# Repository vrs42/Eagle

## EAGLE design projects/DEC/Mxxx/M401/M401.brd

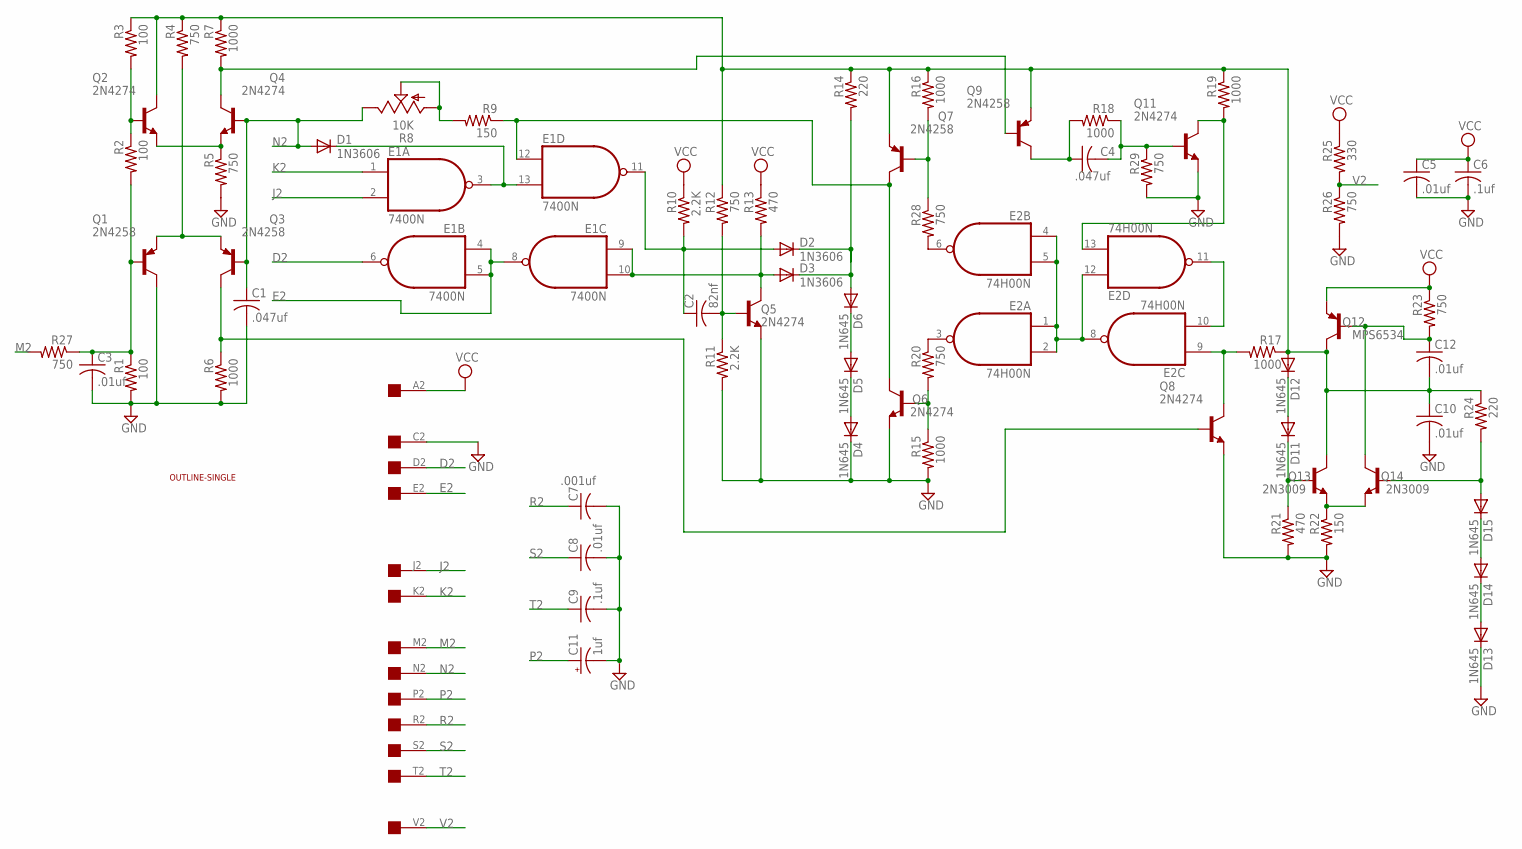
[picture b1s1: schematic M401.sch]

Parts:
C1, C4: .047uf; C050-025X075
C2: 82nf; C050-025X075
C3, C5, C8, C10, C12: .01uf; C050-025X075
C6, C9: .1uf; C050-025X075
C7: .001uf; C050-025X075
C11: 1uf; E15-5
D1, D2, D3: 1N3606; DO35-10
D4, D5, D6, D11, D12, D13, D14, D15: 1N645; DO35-10
E1: 7400N; DIL14
E2: 74H00N; DIL14
Q1, Q3, Q7, Q9: 2N4258; TO39
Q2, Q4, Q5, Q6, Q8, Q11: 2N4274; TO39
Q12: MPS6534; TO39
Q13, Q14: 2N3009; TO39
R1, R2, R3: 100; 0207/10
R4, R5, R12, R20, R23, R26, R27, R28, R29: 750; 0207/10
R6, R7, R15, R16, R17, R18, R19: 1000; 0207/10
R8: 10K; PT-SPIN
R9, R22: 150; 0207/10
R10, R11: 2.2K; 0207/10
R13, R21: 470; 0207/10
R14, R24: 220; 0207/10
R25: 330; 0207/10
U$1: OUTLINE-SINGLE; SINGLE
U$2: EDGE-1; EDGE-CON1

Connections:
D2: E1.6 (O), U$2.D2
E2: E1.4 (I0), E1.5 (I1), E1.8 (O), U$2.E2
GND: C1.2, C3.2, C5.2, C6.2, C7.2, C8.2, C9.2, C10.2, C11.-, D4.C, D13.C, E1.7 (GND), E2.7 (GND), Q1.3 (C), Q5.1 (E), Q6.1 (E), Q8.1 (E), Q11.1 (E), R1.2, R5.2, R6.2, R11.2, R15.2, R21.2, R22.2, R26.2, R29.2, U$2.C2
J2: E1.2 (I1), U$2.J2
K2: E1.1 (I0), U$2.K2
M2: R27.2, U$2.M2
N2: C1.1, D1.A, Q3.2 (B), Q4.2 (B), R8.E, U$2.N2
unnamed: D14.A, D15.C
unnamed: D13.A, D14.C
unnamed: D15.A, Q14.2 (B), R24.2
unnamed: C12.1, Q12.2 (B), Q14.3 (C), R23.2
unnamed: C10.1, C12.2, D12.A, Q2.3 (C), Q7.1 (E), Q9.1 (E), Q12.3 (C), Q13.3 (C), R3.1, R4.1, R7.1, R12.1, R14.1, R16.1, R17.1, R19.1, R24.1
unnamed: D11.C, Q13.2 (B), R21.1
unnamed: Q13.1 (E), Q14.1 (E), R22.1
unnamed: D11.A, D12.C
unnamed: E2.1 (I0), E2.2 (I1), E2.4 (I0), E2.5 (I1), E2.8 (O), E2.12 (I0)
unnamed: C3.1, Q1.2 (B), R1.1, R2.2, R27.1
unnamed: D3.A, E1.9 (I0), E1.10 (I1), Q5.3 (C), R13.2
unnamed: D1.C, E1.3 (O), E1.13 (I1)
unnamed: D4.A, D5.C
unnamed: E2.10 (I1), E2.11 (O)
unnamed: E2.9 (I0), Q8.3 (C), R17.2
unnamed: E2.3 (O), R20.1
unnamed: E2.6 (O), R28.2
unnamed: Q7.2 (B), R16.2, R28.1
unnamed: Q6.2 (B), R15.1, R20.2
unnamed: D5.A, D6.C
unnamed: E1.12 (I0), Q6.3 (C), Q7.3 (C), R9.1
unnamed: C4.1, Q9.3 (C), R18.2
unnamed: C4.2, Q11.2 (B), R18.1, R29.1
unnamed: E2.13 (I1), Q11.3 (C), R19.2
unnamed: D2.C, D3.C, D6.A, R14.2
unnamed: R8.A, R8.S, R9.2
unnamed: C2.2, Q5.2 (B), R11.1, R12.2
unnamed: Q3.3 (C), Q8.2 (B), R6.1
unnamed: C2.1, D2.A, E1.11 (O), R10.2
unnamed: Q1.1 (E), Q3.1 (E), R4.2
unnamed: Q4.3 (C), Q9.2 (B), R7.2
unnamed: Q2.2 (B), R2.1, R3.2
unnamed: Q2.1 (E), Q4.1 (E), R5.1
P2: C11.+, U$2.P2
R2: C7.1, U$2.R2
S2: C8.1, U$2.S2
T2: C9.1, U$2.T2
V2: R25.2, R26.1, U$2.V2
VCC: C5.1, C6.1, E1.14 (VCC), E2.14 (VCC), Q12.1 (E), R10.1, R13.1, R23.1, R25.1, U$2.A2

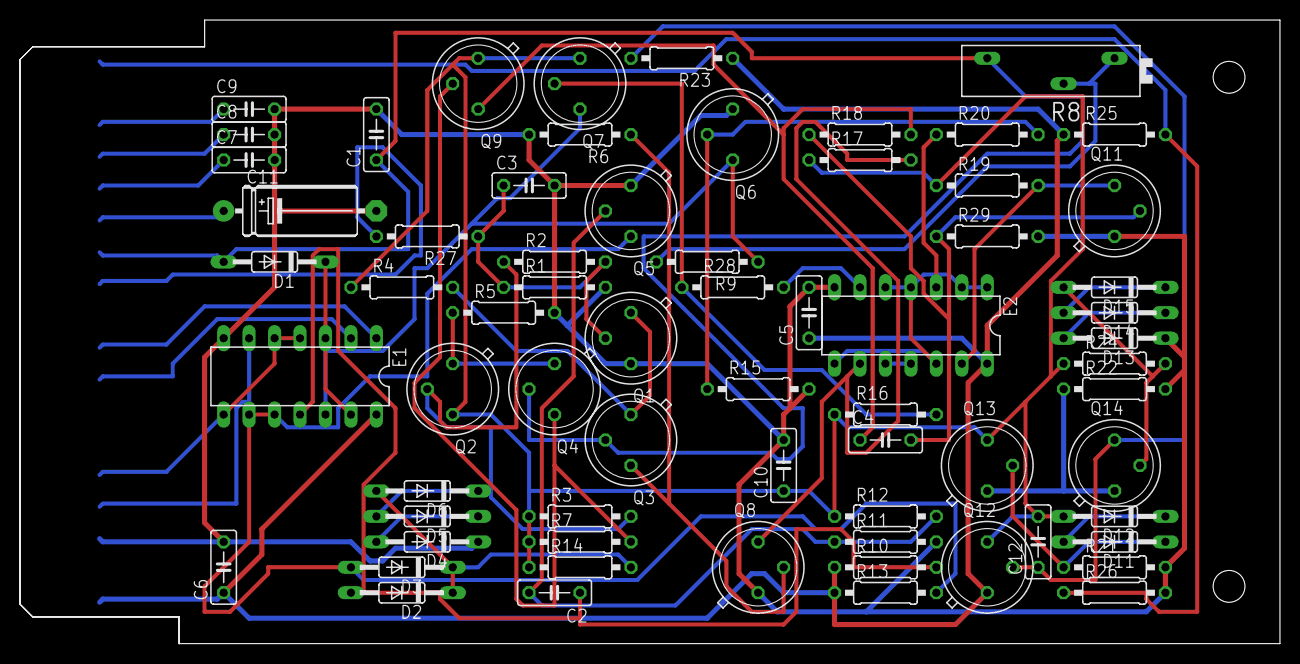
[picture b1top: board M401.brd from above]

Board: 2 copper layers, 125.7 x 62.2 mm, 69 parts (0 on the bottom side), 46 nets.

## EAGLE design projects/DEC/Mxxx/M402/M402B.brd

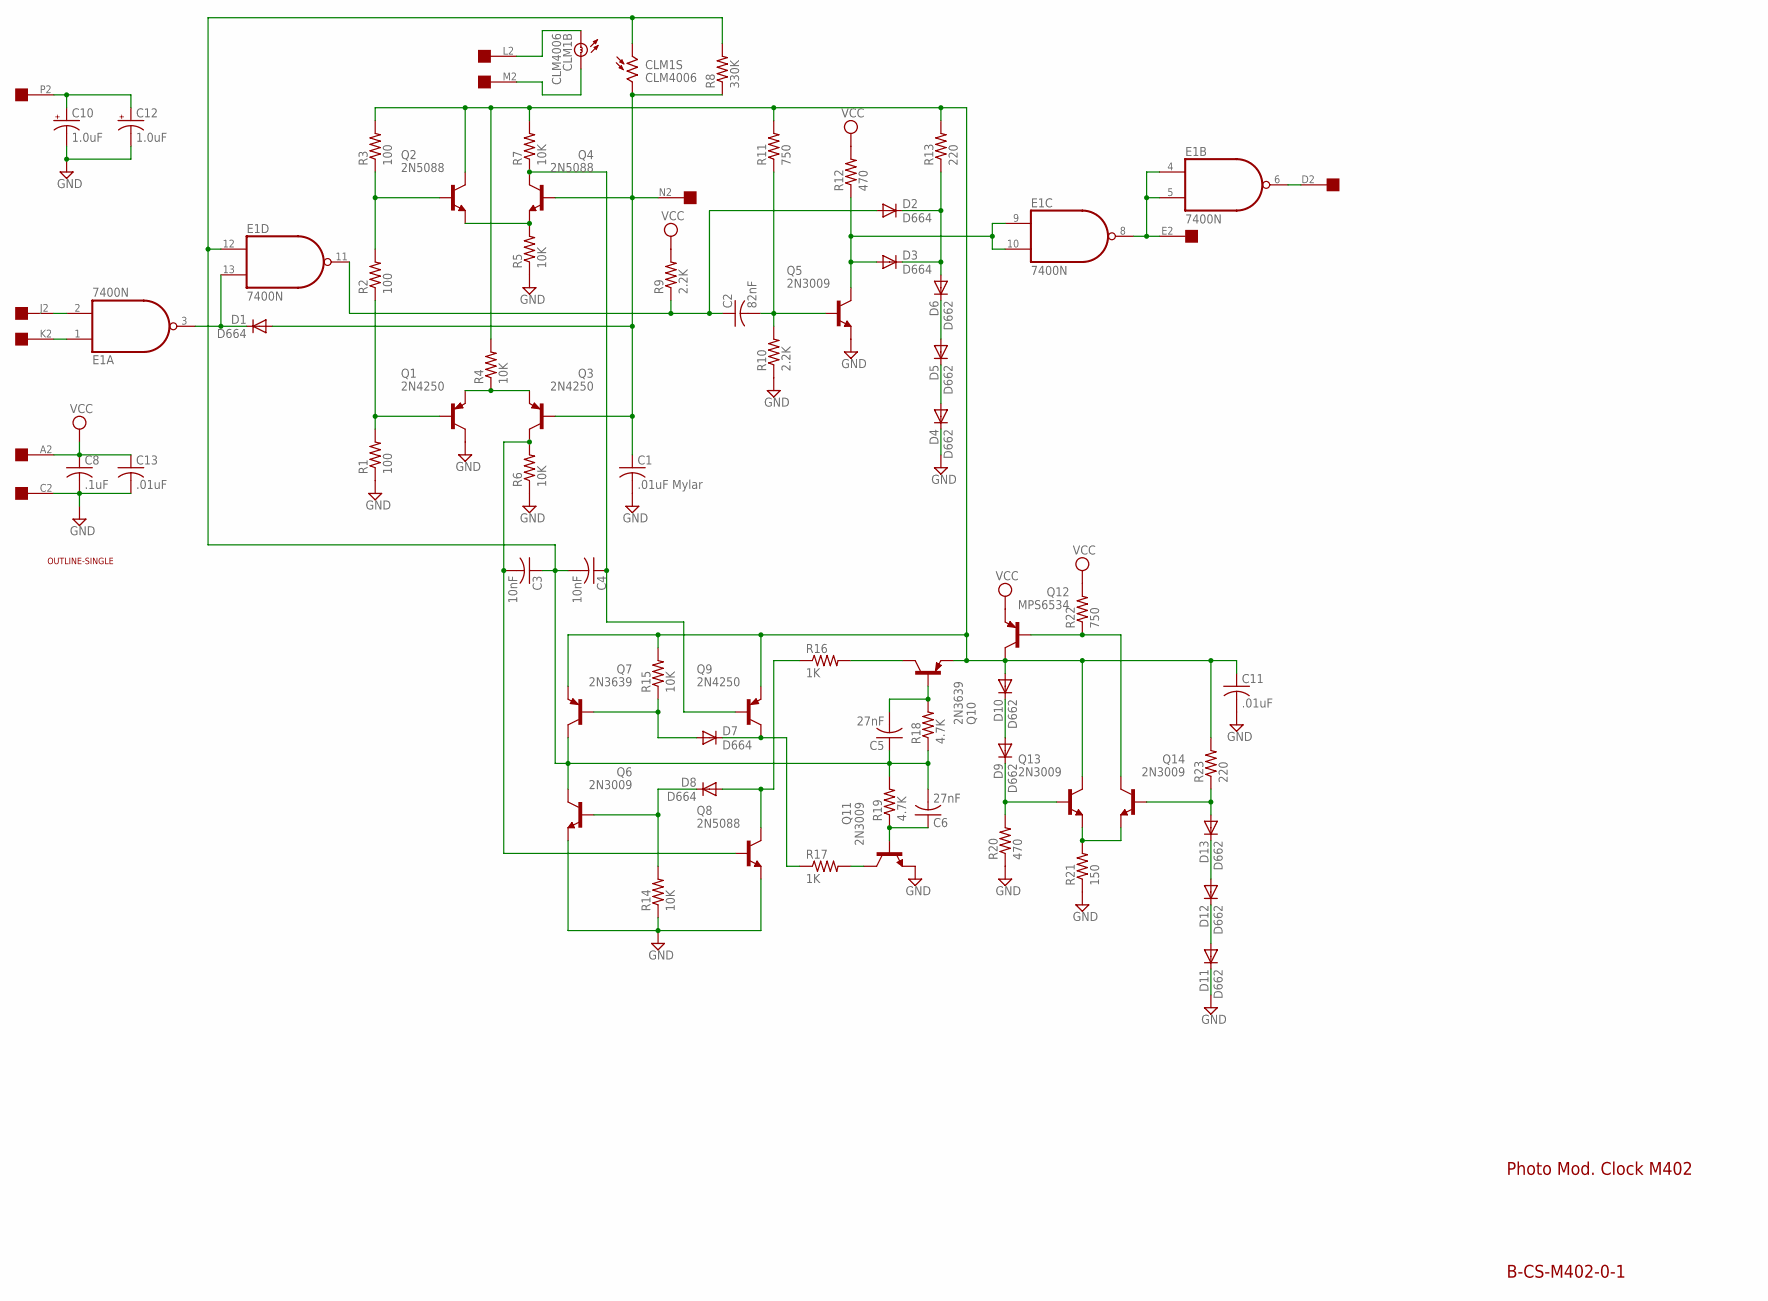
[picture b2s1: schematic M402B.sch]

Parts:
C1: .01uF Mylar; C225-062X268
C2: 82nF; C050-025X075
C3, C4: 10nF; C075-032X103
C5, C6: 27nF; C075-032X103
C8: .1uF; C075-032X103
C10, C12: 1.0uF; E15-5
C11: .01uF; C050-025X075
C13: .01uF; C102-043X133
CLM1: CLM4006
D1, D2, D3, D7, D8: D664; DO35-10
D4, D5, D6, D9, D10, D11, D12, D13: D662; DO35-10
E1: 7400N; DIL14
Q1, Q3, Q9: 2N4250; TO5
Q2, Q4, Q8: 2N5088; TO5
Q5, Q6, Q11, Q13, Q14: 2N3009; TO5
Q7, Q10: 2N3639; TO5
Q12: MPS6534; TO5
R1, R2, R3: 100; 0207/10
R4, R5, R6, R7, R14, R15: 10K; 0207/10
R8: 330K; 0207/10
R9, R10: 2.2K; 0207/10
R11, R22: 750; 0207/10
R12, R20: 470; 0207/10
R13, R23: 220; 0207/10
R16, R17: 1K; 0207/10
R18, R19: 4.7K; 0207/10
R21: 150; 0207/10
U$1: OUTLINE-SINGLE; SINGLE
U$3: EDGE-1; EDGE-CON1

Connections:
GND: C1.2, C8.2, C10.-, C11.2, C12.-, C13.2, D4.C, D11.C, E1.7 (GND), Q1.3 (C), Q5.1 (E), Q6.1 (E), Q8.1 (E), Q11.1 (E), R1.1, R5.1, R6.1, R10.1, R14.1, R20.1, R21.1, U$3.C2
L2: CLM1.B2 (B), U$3.L2
M2: CLM1.B1 (A), U$3.M2
N2: C1.1, CLM1.S2 (2), D1.A, Q3.2 (B), Q4.2 (B), R8.1, U$3.N2
unnamed: E1.4 (I0), E1.5 (I1), E1.8 (O), U$3.E2
unnamed: E1.6 (O), U$3.D2
unnamed: D3.A, E1.9 (I0), E1.10 (I1), Q5.3 (C), R12.1
unnamed: E1.2 (I1), U$3.J2
unnamed: E1.1 (I0), U$3.K2
unnamed: D1.C, E1.3 (O), E1.13 (I1)
unnamed: C10.+, C12.+, U$3.P2
unnamed: D2.C, D3.C, D6.A, R13.1
unnamed: Q2.2 (B), R2.2, R3.1
unnamed: C11.1, D10.A, Q2.3 (C), Q7.1 (E), Q9.1 (E), Q10.1 (E), Q12.3 (C), Q13.3 (C), R3.2, R4.2, R7.2, R11.2, R13.2, R15.2, R23.2
unnamed: C4.1, Q4.3 (C), Q9.2 (B), R7.1
unnamed: Q2.1 (E), Q4.1 (E), R5.2
unnamed: Q1.1 (E), Q3.1 (E), R4.1
unnamed: Q1.2 (B), R1.2, R2.1
unnamed: C3.2, Q3.3 (C), Q8.2 (B), R6.2
unnamed: C2.1, D2.A, E1.11 (O), R9.1
unnamed: C3.1, C4.2, C5.1, C6.2, CLM1.S1 (1), E1.12 (I0), Q6.3 (C), Q7.3 (C), R8.2, R18.1, R19.2
unnamed: C2.2, Q5.2 (B), R10.2, R11.1
unnamed: D11.A, D12.C
unnamed: D4.A, D5.C
unnamed: D5.A, D6.C
unnamed: D12.A, D13.C
unnamed: D13.A, Q14.2 (B), R23.1
unnamed: D9.C, Q13.2 (B), R20.2
unnamed: D9.A, D10.C
unnamed: Q13.1 (E), Q14.1 (E), R21.2
unnamed: Q10.3 (C), R16.2
unnamed: Q12.2 (B), Q14.3 (C), R22.1
unnamed: C6.1, Q11.2 (B), R19.1
unnamed: C5.2, Q10.2 (B), R18.2
unnamed: Q11.3 (C), R17.2
unnamed: D7.A, Q7.2 (B), R15.1
unnamed: D7.C, Q9.3 (C), R17.1
unnamed: D8.C, Q6.2 (B), R14.2
unnamed: D8.A, Q8.3 (C), R16.1
VCC: C8.1, C13.1, E1.14 (VCC), Q12.1 (E), R9.2, R12.2, R22.2, U$3.A2

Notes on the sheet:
B-CS-M402-0-1
Photo Mod. Clock M402

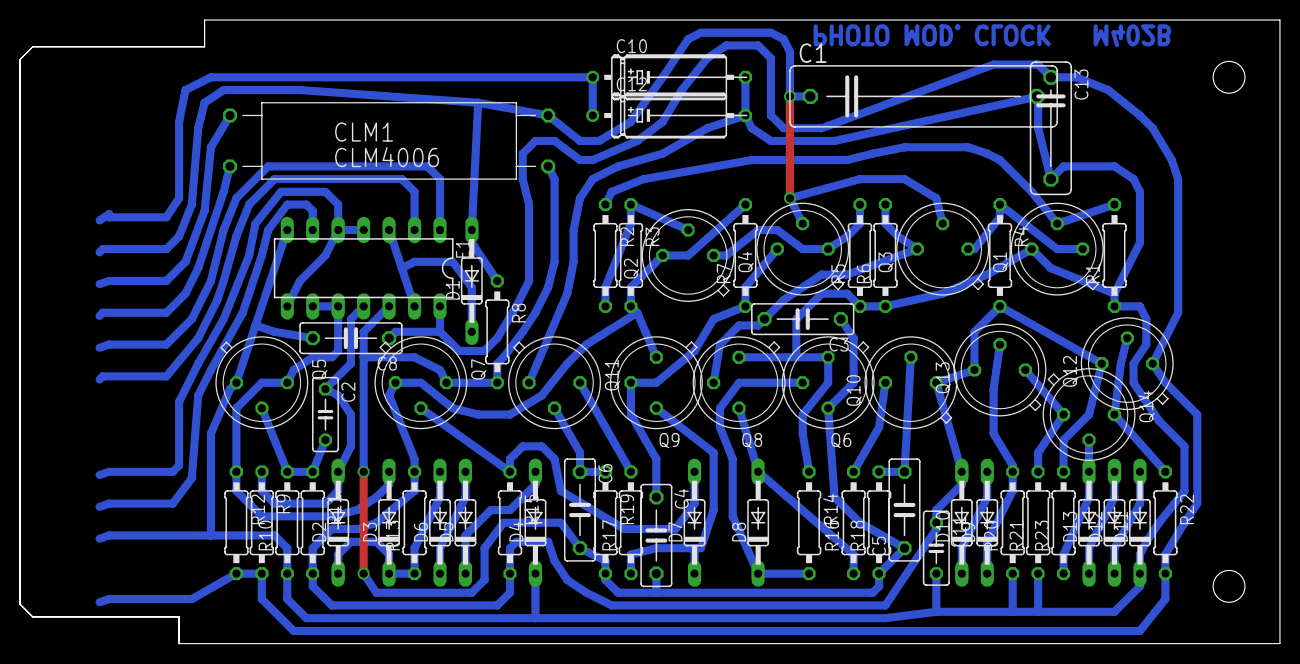
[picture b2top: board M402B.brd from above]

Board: 2 copper layers, 125.7 x 62.2 mm, 65 parts (0 on the bottom side), 40 nets.

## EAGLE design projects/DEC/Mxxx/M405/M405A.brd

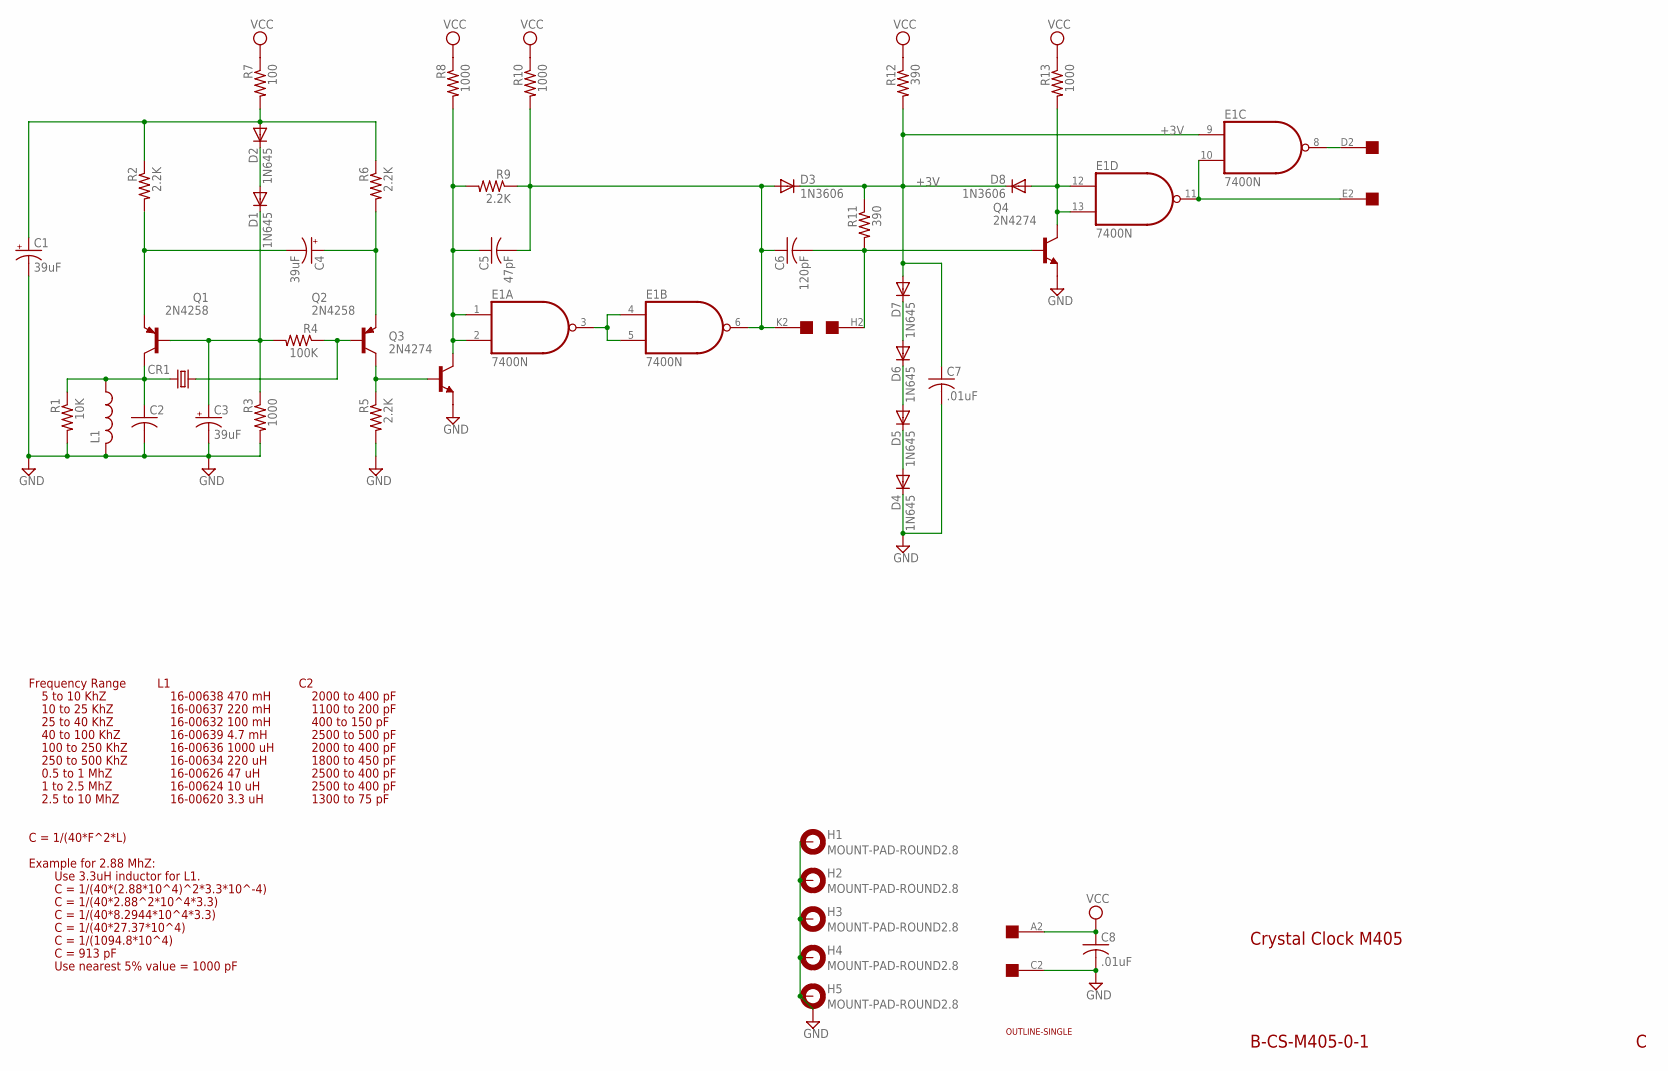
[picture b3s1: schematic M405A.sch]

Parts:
C1, C3, C4: 39uF; E15-5
C2: C-US150-054X183; C150-054X183
C5: 47pF; C050-025X075
C6: 120pF; C050-025X075
C7, C8: .01uF; C050-025X075
CR1: CRYSTALHC13U-H; HC13U-H
D1, D2, D4, D5, D6, D7: 1N645; DO35-10
D3, D8: 1N3606; DO35-10
E1: 7400N; DIL14
H1, H2, H3, H4, H5: MOUNT-PAD-ROUND2.8; 2,8-PAD
L1: L-US0207/12; 0207/12
Q1, Q2: 2N4258; TO39
Q3, Q4: 2N4274; TO39
R1: 10K; 0207/10
R2, R5, R6, R9: 2.2K; 0207/10
R3, R8, R10, R13: 1000; 0207/10
R4: 100K; 0207/10
R7: 100; 0207/10
R11, R12: 390; 0207/10
U$1: OUTLINE-SINGLE; SINGLE
U$2: EDGE-1; EDGE-CON1

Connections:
+3V: C7.1, D3.C, D7.A, D8.C, E1.9 (I0), R11.1, R12.2
GND: C1.-, C2.2, C3.-, C7.2, C8.2, D4.C, E1.7 (GND), H1.B2,8, H2.B2,8, H3.B2,8, H4.B2,8, H5.B2,8, L1.2, Q3.1 (E), Q4.1 (E), R1.2, R3.2, R5.2, U$2.C2
unnamed: CR1.1, Q2.2 (B), R4.1
unnamed: C4.-, Q1.1 (E), R2.2
unnamed: C3.+, D1.C, Q1.2 (B), R3.1, R4.2
unnamed: E1.8 (O), U$2.D2
unnamed: C2.1, CR1.2, L1.1, Q1.3 (C), R1.1
unnamed: D1.A, D2.C
unnamed: E1.10 (I1), E1.11 (O), U$2.E2
unnamed: C4.+, Q2.1 (E), R6.2
unnamed: C1.+, D2.A, R2.1, R6.1, R7.2
unnamed: Q2.3 (C), Q3.2 (B), R5.1
unnamed: C5.1, E1.1 (I0), E1.2 (I1), Q3.3 (C), R8.2, R9.2
unnamed: D8.A, E1.12 (I0), E1.13 (I1), Q4.3 (C), R13.2
unnamed: C5.2, C6.1, D3.A, E1.6 (O), R9.1, R10.2, U$2.K2
unnamed: E1.3 (O), E1.4 (I0), E1.5 (I1)
unnamed: D6.A, D7.C
unnamed: C6.2, Q4.2 (B), R11.2, U$2.H2
unnamed: D5.A, D6.C
unnamed: D4.A, D5.C
VCC: C8.1, E1.14 (VCC), R7.1, R8.1, R10.1, R12.1, R13.1, U$2.A2

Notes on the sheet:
Crystal Clock M405
B-CS-M405-0-1
Frequency Range
16-00638 470 mH
16-00637 220 mH
16-00632 100 mH
16-00639 4.7 mH
16-00636 1000 uH
16-00634 220 uH
16-00626 47 uH
16-00624 10 uH
16-00620 3.3 uH
5 to 10 KhZ
10 to 25 KhZ
25 to 40 KhZ
100 to 250 KhZ
250 to 500 KhZ
0.5 to 1 MhZ
1 to 2.5 MhZ
2.5 to 10 MhZ
40 to 100 KhZ
2000 to 400 pF
1100 to 200 pF
400 to 150 pF
2500 to 500 pF
1800 to 450 pF
2500 to 400 pF
1300 to 75 pF
C = 1/(40*F^2*L)
Example for 2.88 MhZ:
C = 1/(40*(2.88*10^4)^2*3.3*10^-4)
Use 3.3uH inductor for L1.
C = 1/(40*2.88^2*10^4*3.3)
C = 1/(40*8.2944*10^4*3.3)
C = 1/(40*27.37*10^4)
C = 1/(1094.8*10^4)
C = 913 pF
Use nearest 5% value = 1000 pF

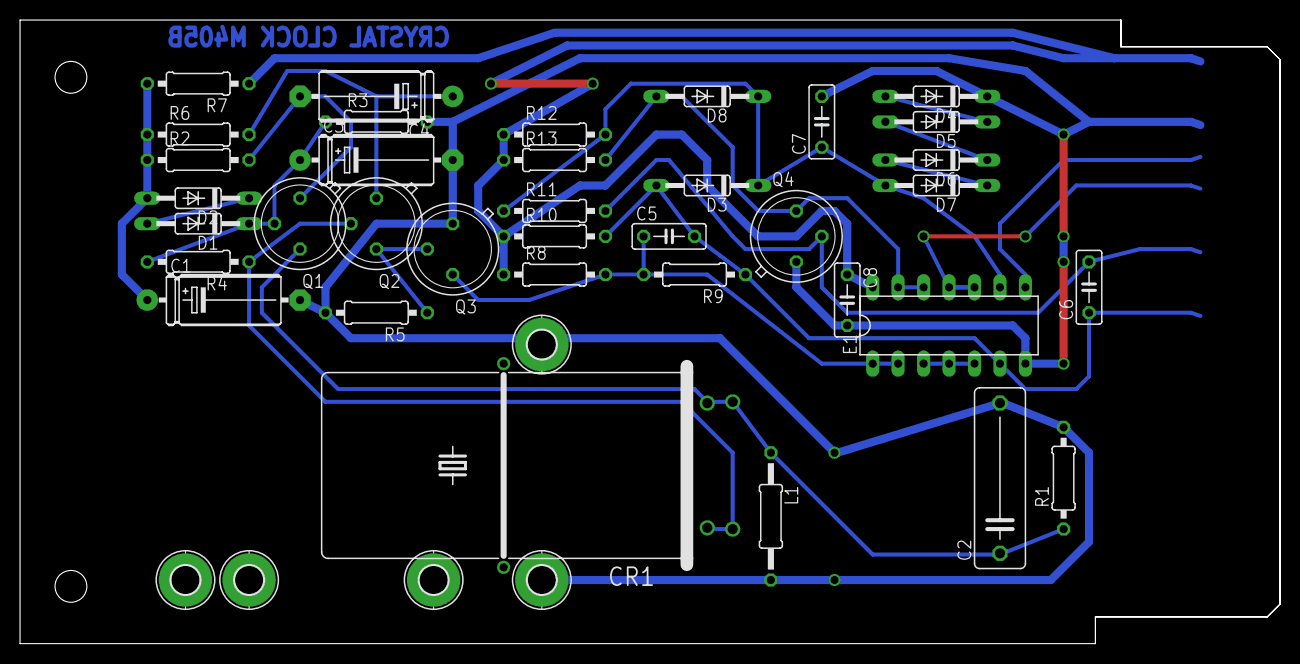
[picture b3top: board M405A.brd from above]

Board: 2 copper layers, 125.7 x 62.2 mm, 43 parts (0 on the bottom side), 21 nets.
